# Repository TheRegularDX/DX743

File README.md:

# DX743
DX743 CORE H7 STM32 development board

features:
- ARM Cortex-M7 processor
- 1MB RAM
- 2MB Flash storage
- A ton of GPIO pins
- Chrom-ART accelerator
- cool logo

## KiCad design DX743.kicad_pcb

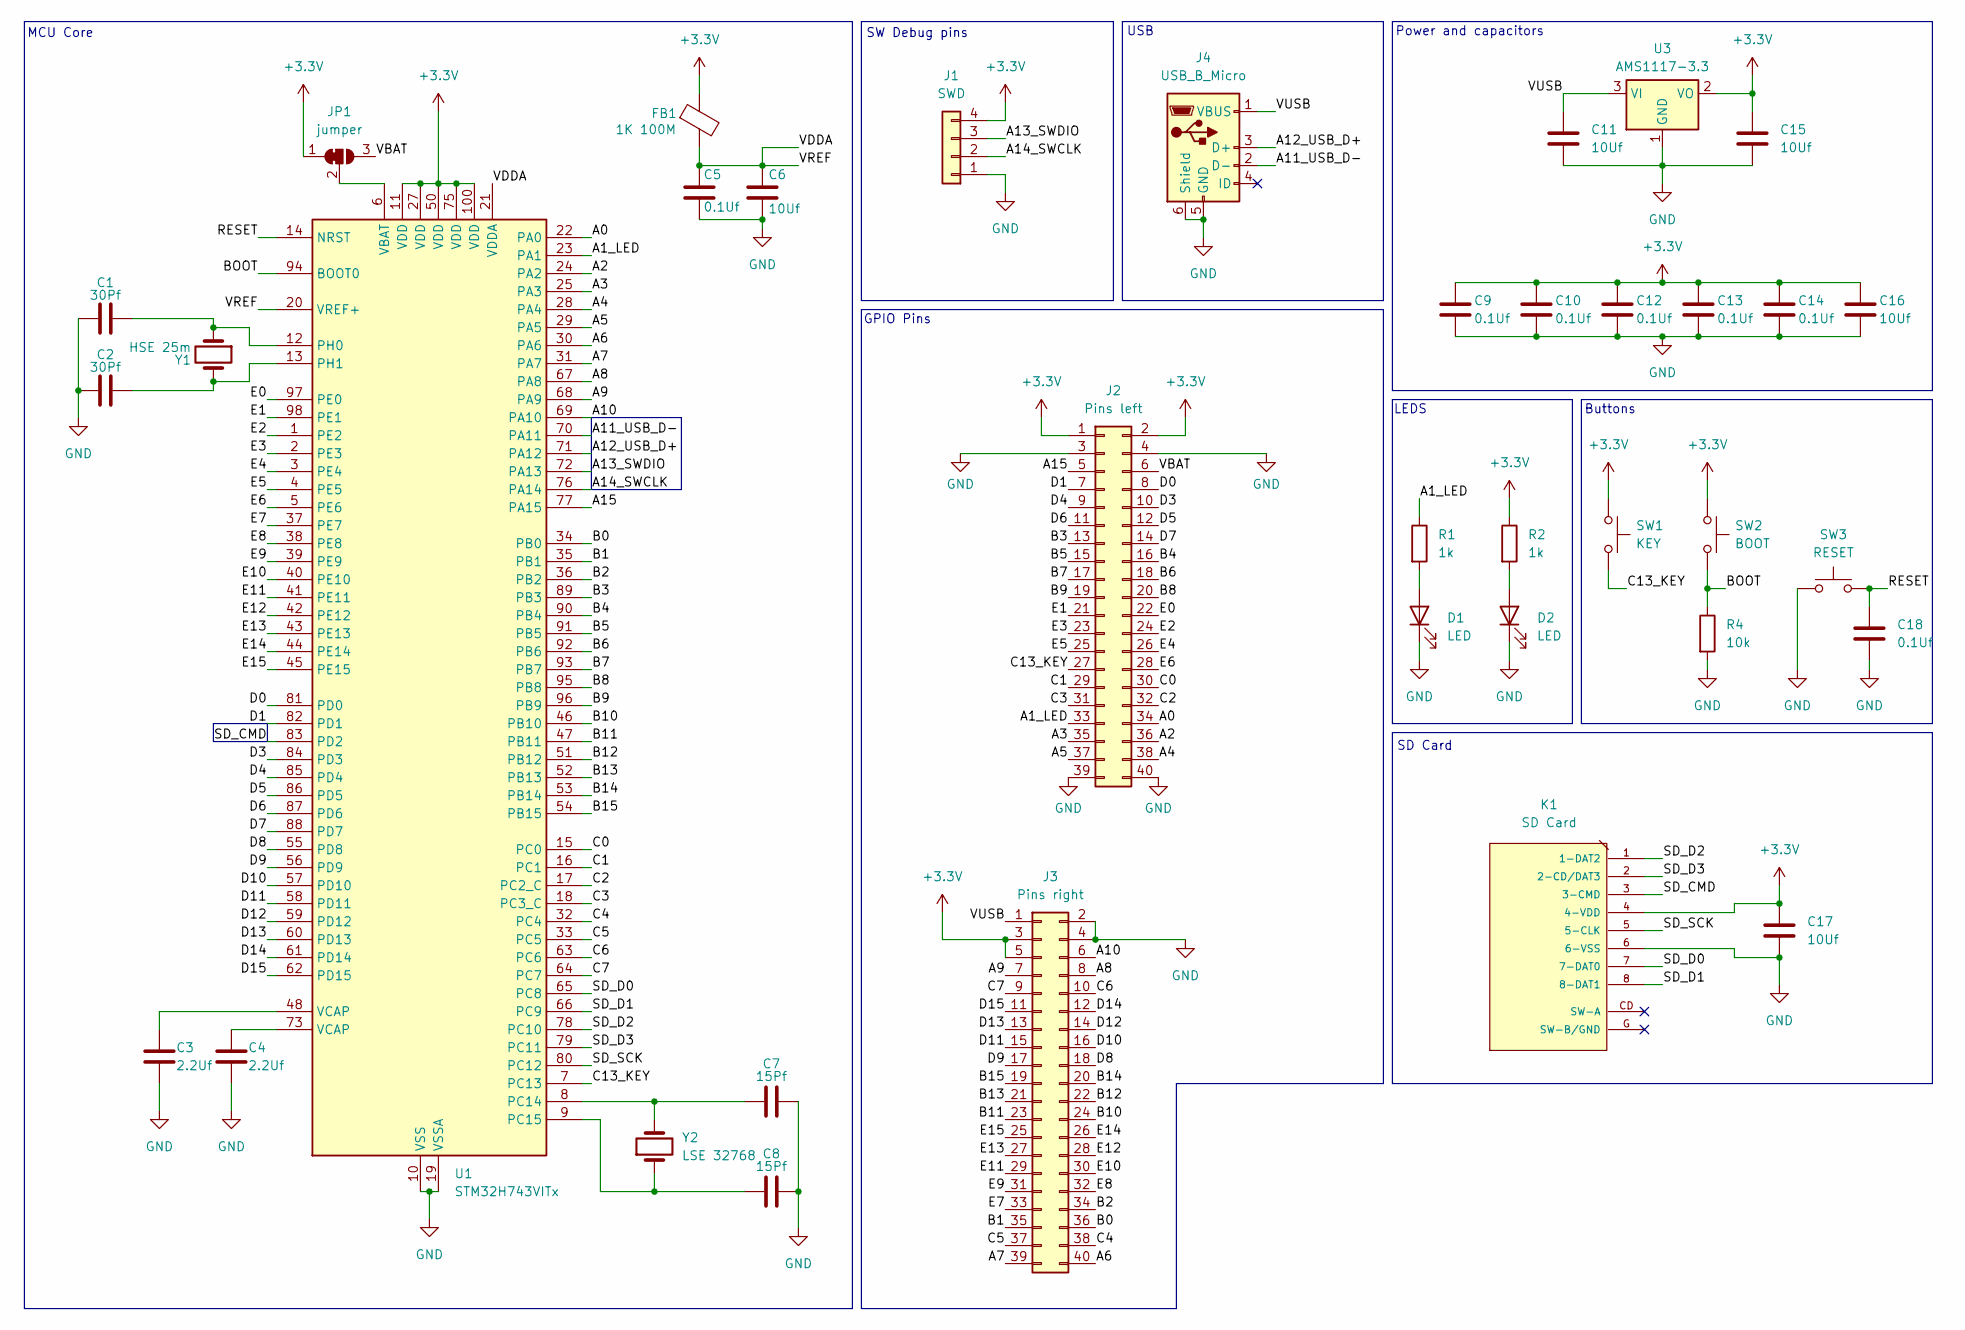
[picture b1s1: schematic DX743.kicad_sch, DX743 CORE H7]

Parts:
C1, C2: 30Pf; C_0805_2012Metric
C3, C4: 2.2Uf; C_0603_1608Metric
C5, C9, C10, C12, C13, C14, C18: 0.1Uf; C_0603_1608Metric
C6, C11, C15, C16, C17: 10Uf; C_0805_2012Metric
C7, C8: 15Pf; C_0603_1608Metric
D1, D2: LED; LED_0805_2012Metric
FB1: 1K 100M; L_0805_2012Metric
J1: SWD; PinHeader_1x04_P2.54mm_Horizontal
J2: Pins left; PinHeader_2x20_P2.54mm_Vertical
J3: Pins right; PinHeader_2x20_P2.54mm_Vertical
J4: USB_B_Micro; USB_Micro-B_Molex-105017-0001
JP1: jumper; SolderJumper-3_P1.3mm_Bridged12_Pad1.0x1.5mm
K1: SD Card; 112J-TDAR-R01
R1, R2: 1k; R_0805_2012Metric
R4: 10k; R_0805_2012Metric
SW1: KEY; SW_Push_SPST_NO_Alps_SKRK
SW2: BOOT; SW_Push_SPST_NO_Alps_SKRK
SW3: RESET; SW_Push_SPST_NO_Alps_SKRK
U1: STM32H743VITx; LQFP-100_14x14mm_P0.5mm
U3: AMS1117-3.3; SOT-223-3_TabPin2
Y1: HSE 25m; Crystal_HC49-U_Vertical
Y2: LSE 32768; Crystal_SMD_3215-2Pin_3.2x1.5mm

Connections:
+3.3V: C9.1, C10.1, C12.1, C13.1, C14.1, C15.1, C16.1, C17.1, FB1.1, J1.4, J2.1, J2.2, J3.3, J3.5, JP1.1 (A), K1.4 (4-VDD), R2.1, SW1.1, SW2.1, U1.11 (VDD), U1.27 (VDD), U1.50 (VDD), U1.75 (VDD), U1.100 (VDD), U3.2 (VO)
/A0: J2.34, U1.22 (PA0)
/A1_LED: J2.33, R1.1, U1.23 (PA1)
/A2: J2.36, U1.24 (PA2)
/A3: J2.35, U1.25 (PA3)
/A4: J2.38, U1.28 (PA4)
/A5: J2.37, U1.29 (PA5)
/A6: J3.40, U1.30 (PA6)
/A7: J3.39, U1.31 (PA7)
/A8: J3.8, U1.67 (PA8)
/A9: J3.7, U1.68 (PA9)
/A10: J3.6, U1.69 (PA10)
/A11_USB_D-: J4.2 (D-), U1.70 (PA11)
/A12_USB_D+: J4.3 (D+), U1.71 (PA12)
/A13_SWDIO: J1.3, U1.72 (PA13)
/A14_SWCLK: J1.2, U1.76 (PA14)
/A15: J2.5, U1.77 (PA15)
/B0: J3.36, U1.34 (PB0)
/B1: J3.35, U1.35 (PB1)
/B2: J3.34, U1.36 (PB2)
/B3: J2.13, U1.89 (PB3)
/B4: J2.16, U1.90 (PB4)
/B5: J2.15, U1.91 (PB5)
/B6: J2.18, U1.92 (PB6)
/B7: J2.17, U1.93 (PB7)
/B8: J2.20, U1.95 (PB8)
/B9: J2.19, U1.96 (PB9)
/B10: J3.24, U1.46 (PB10)
/B11: J3.23, U1.47 (PB11)
/B12: J3.22, U1.51 (PB12)
/B13: J3.21, U1.52 (PB13)
/B14: J3.20, U1.53 (PB14)
/B15: J3.19, U1.54 (PB15)
/BOOT: R4.1, SW2.2, U1.94 (BOOT0)
/C0: J2.30, U1.15 (PC0)
/C1: J2.29, U1.16 (PC1)
/C2: J2.32, U1.17 (PC2_C)
/C3: J2.31, U1.18 (PC3_C)
/C4: J3.38, U1.32 (PC4)
/C5: J3.37, U1.33 (PC5)
/C6: J3.10, U1.63 (PC6)
/C7: J3.9, U1.64 (PC7)
/C13_KEY: J2.27, SW1.2, U1.7 (PC13)
/D0: J2.8, U1.81 (PD0)
/D1: J2.7, U1.82 (PD1)
/D3: J2.10, U1.84 (PD3)
/D4: J2.9, U1.85 (PD4)
/D5: J2.12, U1.86 (PD5)
/D6: J2.11, U1.87 (PD6)
/D7: J2.14, U1.88 (PD7)
/D8: J3.18, U1.55 (PD8)
/D9: J3.17, U1.56 (PD9)
/D10: J3.16, U1.57 (PD10)
/D11: J3.15, U1.58 (PD11)
/D12: J3.14, U1.59 (PD12)
/D13: J3.13, U1.60 (PD13)
/D14: J3.12, U1.61 (PD14)
/D15: J3.11, U1.62 (PD15)
/E0: J2.22, U1.97 (PE0)
/E1: J2.21, U1.98 (PE1)
/E2: J2.24, U1.1 (PE2)
/E3: J2.23, U1.2 (PE3)
/E4: J2.26, U1.3 (PE4)
/E5: J2.25, U1.4 (PE5)
/E6: J2.28, U1.5 (PE6)
/E7: J3.33, U1.37 (PE7)
/E8: J3.32, U1.38 (PE8)
/E9: J3.31, U1.39 (PE9)
/E10: J3.30, U1.40 (PE10)
/E11: J3.29, U1.41 (PE11)
/E12: J3.28, U1.42 (PE12)
/E13: J3.27, U1.43 (PE13)
/E14: J3.26, U1.44 (PE14)
/E15: J3.25, U1.45 (PE15)
/RESET: C18.1, SW3.2, U1.14 (NRST)
/SD_CMD: K1.3 (3-CMD), U1.83 (PD2)
/SD_D0: K1.7 (7-DAT0), U1.65 (PC8)
/SD_D1: K1.8 (8-DAT1), U1.66 (PC9)
/SD_D2: K1.1 (1-DAT2), U1.78 (PC10)
/SD_D3: K1.2 (2-CD/DAT3), U1.79 (PC11)
/SD_SCK: K1.5 (5-CLK), U1.80 (PC12)
/VBAT: J2.6, JP1.3 (B)
/VDDA: C5.1, C6.1, FB1.2, U1.20 (VREF+), U1.21 (VDDA)
/VUSB: C11.1, J3.1, J4.1 (VBUS), U3.3 (VI)
GND: C1.1, C2.1, C3.2, C4.2, C5.2, C6.2, C7.2, C8.2, C9.2, C10.2, C11.2, C12.2, C13.2, C14.2, C15.2, C16.2, C17.2, C18.2, D1.1 (K), D2.1 (K), J1.1, J2.3, J2.4, J2.39, J2.40, J3.2, J3.4, J4.5 (GND), J4.6 (Shield), K1.6 (6-VSS), R4.2, SW3.1, U1.10 (VSS), U1.19 (VSSA), U1.26 (VSS), U1.49 (VSS), U1.74 (VSS), U1.99 (VSS), U3.1 (GND)
unnamed: C3.1, U1.48 (VCAP)
unnamed: C4.1, U1.73 (VCAP)
unnamed: D1.2 (A), R1.2
unnamed: D2.2 (A), R2.2
unnamed: JP1.2 (C), U1.6 (VBAT)
unnamed: C7.1, U1.8 (PC14), Y2.2
unnamed: C8.1, U1.9 (PC15), Y2.1
unnamed: C1.2, U1.12 (PH0), Y1.1
unnamed: C2.2, U1.13 (PH1), Y1.2

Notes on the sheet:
GPIO Pins
MCU Core
Buttons
USB
SD Card
LEDS
SW Debug pins
Power and capacitors

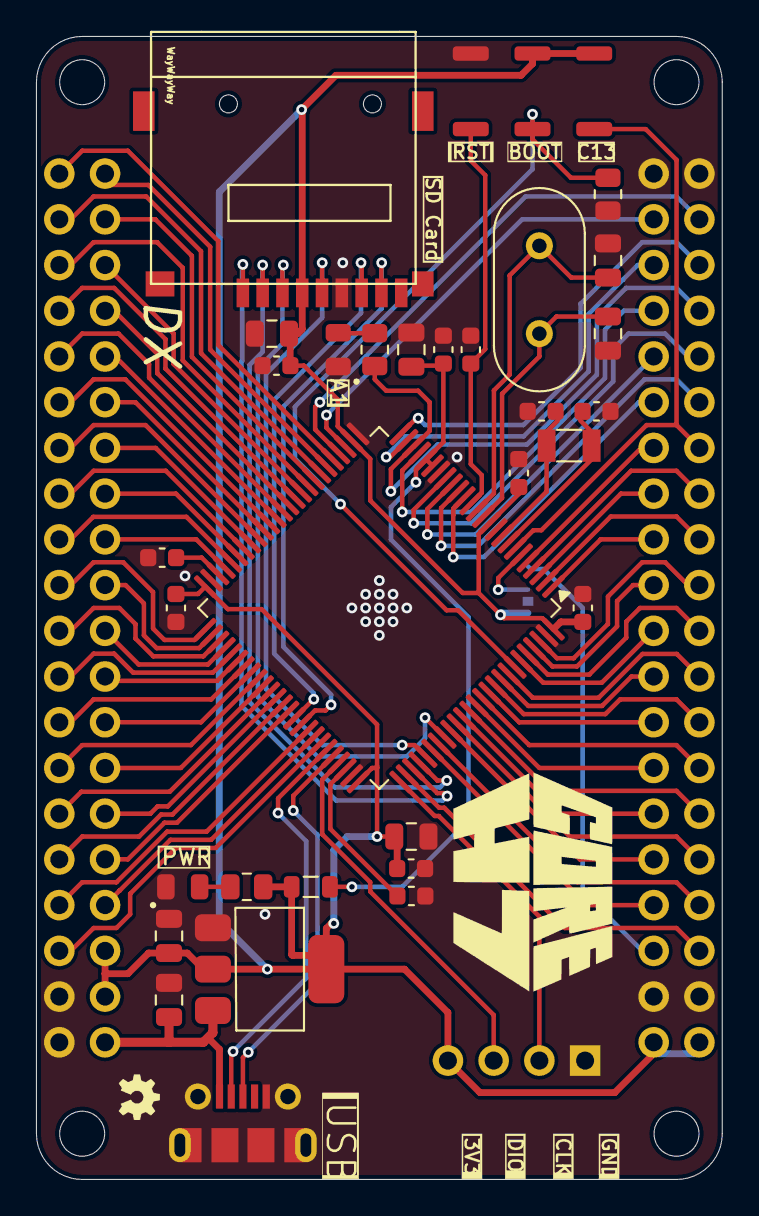
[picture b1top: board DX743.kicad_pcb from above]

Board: 2 copper layers, 38.1 x 63.5 mm, 37 parts (1 on the bottom side), 94 nets.
